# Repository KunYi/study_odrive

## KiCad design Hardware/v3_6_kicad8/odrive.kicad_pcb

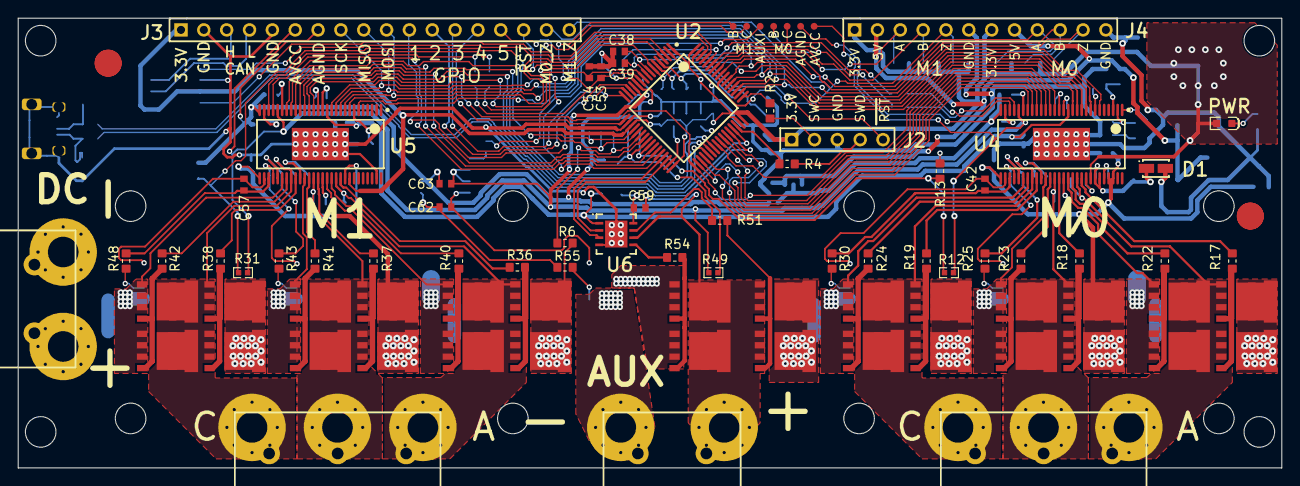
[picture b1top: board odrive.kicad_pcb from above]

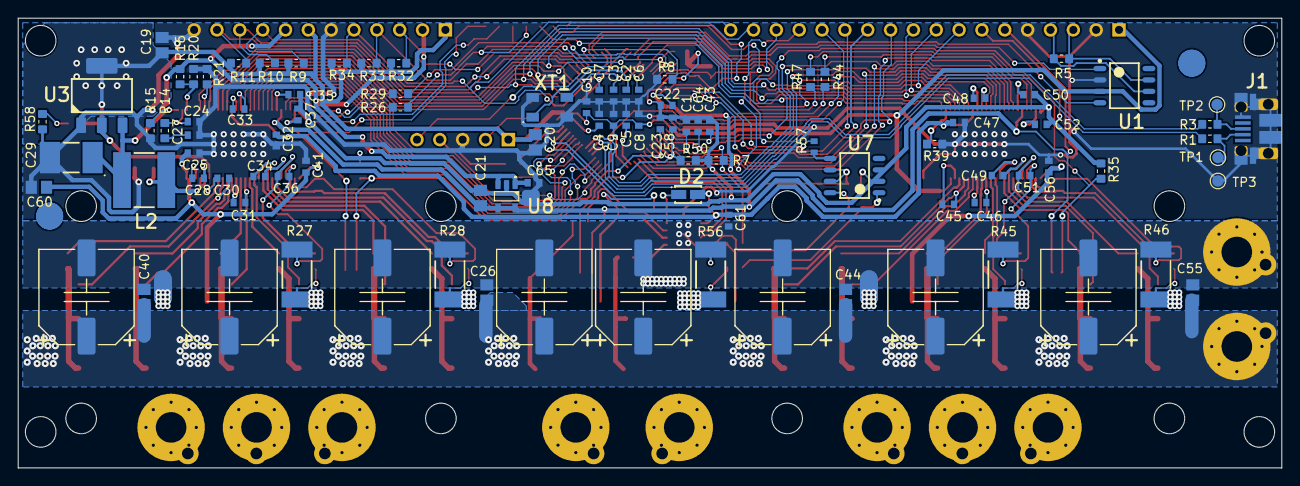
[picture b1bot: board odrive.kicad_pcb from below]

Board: 2 copper layers, 140.5 x 50.0 mm, 217 parts (109 on the bottom side), 152 nets.

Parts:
C1, C4, C5, C23, C32, C35, C37, C43, C47, C50, C52, C58, C61, C65: 2.2µF; CAPC1608X09L
C2, C3: 10pF; CAPC1608X09L
C6, C7, C8, C9, C10, C22, C25, C28, C30, C31, C34, C41, C45, C46, C49, C56, C59, C63: 0.1uF; CAPC1608X09L
C11, C12, C13, C14, C15, C16, C17, C18: 470uF; CAP_ELEC_SIZE_G
C19, C20, C21, C26, C40, C44, C55, C60: 4.7uF; CAPC2012X09N
C24: 82pF; CAPC1608X09L
C27: 270pF; CAPC1608X09L
C29: 68uF; CAPCP6032X28N
C33, C48: 0.022µF; CAPC1608X09L
C36, C38, C39, C42, C51, C53, C54, C57, C62, C64: 2200pF; CAPC1608X09L
D1, D2: DIOM2717X10N
FID1, FID2, FID3, FID4: FIDUCIAL
H1, H2, H3, H4, H5, H6, H7, H8, H9, H10, H11, H12: M3 Hole
J1: USB_0103594-0001LF
J2: HDR1X5
J3: Leftheader; HDR1X18
J4: Rightheader; HDR1X12
J7, J8, J11, J12, J13, J16, J17, J18, J21, J22: M3 Spade Hole
J9, J23: 1868076
J14, J19: 1704936
L2: 22uH; INDC6060X28N
LED1: Green; LED-0603-GREEN
NT1: NetTie_2mm
NT2, NT3, NT4, NT5, NT6, NT7, NT8, NT9, NT10, NT11: 0.25mm; NetTie_0.25mm
Q1, Q3, Q5, Q7, Q8, Q9, Q10, Q11, Q12, Q13, Q15, Q17, Q19, Q20, Q21, Q22, Q23, Q24, Q26, Q27, Q28: SO8FL
Q2, Q4, Q6, Q14, Q16, Q18, Q25: FILL_FOOTPRINT; SO8FL_FILL
R1, R2, R3, R4, R26, R29, R44, R47: 22R; RESC1608X55N
R5, R25, R30, R43, R48, R55: 120R; RESC1608X55N
R6: 10K; RESC1608X55N
R7, R58: 1k; RESC1608X55N
R8, R14: 47K; RESC1608X55N
R9, R10, R11, R13, R20, R32, R33, R34, R35, R50: 3.3k; RESC1608X55N
R12, R31, R49: 10k; RESC1005X40N
R15: 220k; RESC1608X55N
R16, R21, R39: 18k; RESC1608X55N
R17, R18, R19, R22, R23, R24, R36, R37, R38, R40, R41, R42, R51, R54: 2.2R; RESC1608X55N
R27, R28, R45, R46, R56: 500uOhm; RESC6432X09N
R57: 120R; RESC1608X06L
TP1, TP2, TP3: TESTPOINT; TP-R60
TP4, TP5, TP6, TP7, TP8, TP9, TP10: TESTPOINT; TP-R30
U1: SN65HVD232D; SOIC127P600X175-8N
U2: STM-LQFP64_N
U3: 3.3V; SOT223
U4, U5: TSSOP50P810X120_HS-57N
U6: SON80P400X80_HS-9N
U7: SOIC127P600X175-8N
U8: 3.3V; SOT23-5
XT1: 8 MHz; DFN220P320X110-4N

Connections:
5V: C29.1, C65.2, J4.2, J4.8, L2.2, R16.1, U3.3, U8.1, U8.3
AGND: C1.1, C21.1, C22.2, C23.1, C35.1, C37.1, C38.2, C39.2, C43.1, C50.1, C52.1, C53.2, C54.2, C58.1, C63.2, C64.2, J3.7, NT1.2, R7.1, R13.2, R35.2, R50.2, TP5.1, U2.12, U4.28, U5.28, U7.2, U7.3, U8.2
AUX_H_1: U2.30, U6.2
AUX_I_1: C64.1, R57.2, TP10.1, U2.21
AUX_L_1: U2.29, U6.3
AUX_TEMP_1: C58.2, R49.1, R50.1, U2.24
AVCC: C21.2, C22.1, C63.1, J3.6, R12.2, R31.2, R49.2, TP4.1, U2.13, U4.24, U5.24, U7.6, U7.7, U8.4, U8.5
BOOT0_1: R8.2, U2.60
CAN_D_1: U1.1, U2.62
CAN_H_1: J3.3, R5.2, U1.7
CAN_L_1: J3.4, R5.1, U1.6
CAN_R_1: U1.4, U2.61
DCBUS: C11.1, C12.1, C13.1, C14.1, C15.1, C16.1, C17.1, C18.1, C25.1, C26.2, C40.2, C41.1, C44.2, C55.2, C56.1, C60.2, J7.1, J9.2, Q1.D, Q2.D, Q3.D, Q4.D, Q5.D, Q6.D, Q13.D, Q14.D, Q15.D, Q16.D, Q17.D, Q18.D, Q25.D, Q26.D, R6.2, U4.29, U4.53, U4.54, U5.29
EN_GATE_1: U2.33, U4.16, U5.16
GH_A_2: R17.2, U4.47
GH_A_3: R36.1, U5.47
GH_B_2: R18.2, U4.42
GH_B_3: R37.1, U5.42
GH_C_2: R19.2, U4.37
GH_C_3: R38.1, U5.37
GL_A_2: R22.2, U4.45
GL_A_3: R40.1, U5.45
GL_B_2: R23.2, U4.40
GL_B_3: R41.1, U5.40
GL_C_2: R24.2, U4.35
GL_C_3: R42.1, U5.35
GND: C2.2, C3.2, C4.1, C5.1, C6.1, C7.2, C8.2, C9.2, C10.2, C19.1, C20.1, C24.2, C25.2, C27.2, C29.2, C32.1, C41.2, C47.1, C56.2, C60.1, C65.1, D1.A, J1.5, J1.SH, J2.3, J3.2, J3.5, J4.6, J4.12, NT1.1, NT7.1, R8.1, R15.2, R20.2, R21.2, R39.2, R58.2, TP3.1, U1.2, U2.18, U2.63, U3.1, U4.57, U5.55, U5.57, XT1.G
GPIO_1_1: J3.11, U2.14
GPIO_2_1: J3.12, U2.15
GPIO_3_1: J3.13, U2.16
GPIO_4_1: J3.14, U2.17
GPIO_5_1: J3.15, U2.28
GVDD: C32.2, C47.2, C61.2, D2.A, U4.13, U5.13, U6.1
M0_AH_1: U2.41, U4.17
M0_AL_1: U2.34, U4.18
M0_BH_1: U2.42, U4.19
M0_BL_1: U2.35, U4.20
M0_CH_1: U2.43, U4.21
M0_CL_1: U2.36, U4.22
M0_DC_CAL_1: U2.40, U4.12
M0_ENC_A_1: J4.9, R9.1, U2.56
M0_ENC_B_1: J4.10, R10.1, U2.57
M0_ENC_Z_1: J3.17, J4.11, R11.1, U2.50
M0_NCS_1: U2.2, U4.8
M0_SO1_1: C38.1, R26.2, TP6.1, U2.8
M0_SO2_1: C39.1, R29.2, TP7.1, U2.9
M0_TEMP_1: C23.2, R12.1, R13.1, U2.25
M1_AH_1: U2.37, U5.17
M1_AL_1: U2.23, U5.18
M1_BH_1: U2.38, U5.19
M1_BL_1: U2.26, U5.20
M1_CH_1: U2.39, U5.21
M1_CL_1: U2.27, U5.22
M1_DC_CAL_1: U2.4, U5.12
M1_ENC_A_1: J4.3, R32.2, U2.58
M1_ENC_B_1: J4.4, R33.2, U2.59
M1_ENC_Z_1: J3.18, J4.5, R34.2, U2.55
M1_NCS_1: U2.3, U5.8
M1_SO1_1: C53.1, R44.2, TP8.1, U2.11
M1_SO2_1: C54.1, R47.2, TP9.1, U2.10
M1_TEMP_1: C43.2, R31.1, R35.1, U2.20
NFAULT_1: U2.54, U4.6, U5.6
NRST_1: C6.2, J2.5, J3.16, U2.7
NetC2_1: C2.1, U2.6, XT1.1
NetC3_1: C3.1, U2.5, XT1.3
NetC4_2: C4.2, U2.47
NetC5_2: C5.2, U2.31
NetC24_1: C24.1, R14.1, U4.2
NetC27_1: C27.1, R14.2
NetC28_1: C28.1, D1.K, L2.1, U4.50, U4.51
NetC28_2: C28.2, U4.52
NetC30_2: C30.2, U4.48
NetC31_2: C31.2, U4.43
NetC33_1: C33.1, U4.14
NetC33_2: C33.2, U4.15
NetC34_2: C34.2, U4.38
NetC35_2: C35.2, U4.23
NetC36_1: C36.1, R25.2, U4.33
NetC37_2: C37.2, U4.27
NetC42_1: C42.1, R30.2, U4.31
NetC45_2: C45.2, U5.48
NetC46_2: C46.2, U5.43
NetC48_1: C48.1, U5.14
NetC48_2: C48.2, U5.15
NetC49_2: C49.2, U5.38
NetC50_2: C50.2, U5.23
NetC51_1: C51.1, R43.2, U5.33
NetC52_2: C52.2, U5.27
NetC57_1: C57.1, R48.2, U5.31
NetC59_1: C59.1, D2.K, U6.8
NetC59_2: C59.2, J21.1, J23.2, Q25.S, Q26.S, Q27.D, Q28.D, U6.6
NetC62_1: C62.1, R55.1, U7.1
NetC62_2: C62.2, NT6.1, U7.8
NetJ1_2: J1.2, R1.2, TP1.1
NetJ1_3: J1.3, R3.2, TP2.1
NetJ2_2: J2.2, R2.1
NetJ2_4: J2.4, R4.1
NetJ22_1: J22.1, J23.1, R55.2, R56.1
NetLED1_K: LED1.K, R58.1
NetQ1_G: Q1.G, Q2.G, R17.1
NetQ3_G: Q3.G, Q4.G, R18.1
NetQ5_G: Q5.G, Q6.G, R19.1
NetQ7_G: Q7.G, Q8.G, R22.1
NetQ9_G: Q9.G, Q10.G, R23.1
NetQ11_G: Q11.G, Q12.G, R24.1
NetQ13_G: Q13.G, Q14.G, R36.2
NetQ15_G: Q15.G, Q16.G, R37.2
NetQ17_G: Q17.G, Q18.G, R38.2
NetQ19_G: Q19.G, Q20.G, R40.2
NetQ21_G: Q21.G, Q22.G, R41.2
NetQ23_G: Q23.G, Q24.G, R42.2
NetQ25_G: Q25.G, Q26.G, R51.2
NetQ27_G: Q27.G, Q28.G, R54.2
NetR15_1: R15.1, U4.1
NetR16_2: R16.2, R20.1, U4.3
NetR21_1: R21.1, U4.7
NetR26_1: R26.1, U4.25
NetR29_1: R29.1, U4.26
NetR39_1: R39.1, U5.7
NetR44_1: R44.1, U5.25
NetR47_1: R47.1, U5.26
NetR51_1: R51.1, U6.7
NetR54_1: R54.1, U6.5
NetR57_1: R57.1, U7.5
PGND: C11.2, C12.2, C13.2, C14.2, C15.2, C16.2, C17.2, C18.2, C26.1, C40.1, C44.1, C55.1, C61.1, J8.1, J9.1, NT2.2, NT3.2, NT4.2, NT5.2, NT6.2, NT7.2, Q7.S, Q8.S, Q19.S, Q20.S, Q27.S, Q28.S, R27.1, R28.1, R45.1, R46.1, R56.2, U4.44, U5.44, U6.4, U6.9
SH_A_2: C30.1, J11.1, J14.3, Q1.S, Q2.S, Q7.D, Q8.D, U4.46
SH_A_3: C45.1, J16.1, J19.3, Q13.S, Q14.S, Q19.D, Q20.D, U5.46
SH_B_2: C31.1, J12.1, J14.2, Q3.S, Q4.S, Q9.D, Q10.D, U4.41
SH_B_3: C46.1, J17.1, J19.2, Q15.S, Q16.S, Q21.D, Q22.D, U5.41
SH_C_2: C34.1, J13.1, J14.1, Q5.S, Q6.S, Q11.D, Q12.D, U4.36
SH_C_3: C49.1, J18.1, J19.1, Q17.S, Q18.S, Q23.D, Q24.D, U5.36
SL_B_2: NT8.2, Q9.S, Q10.S, R27.2, U4.39
SL_B_3: NT10.2, Q21.S, Q22.S, R45.2, U5.39
SL_C_2: NT9.2, Q11.S, Q12.S, R28.2, U4.34
SL_C_3: NT11.2, Q23.S, Q24.S, R46.2, U5.34
SN1_2: NT8.1, R25.1
SN1_3: NT10.1, R43.1
SN2_2: NT9.1, R30.1
SN2_3: NT11.1, R48.1
SP1_2: C36.2, NT2.1, U4.32
SP1_3: C51.2, NT4.1, U5.32
SP2_2: C42.2, NT3.1, U4.30
SP2_3: C57.2, NT5.1, U5.30
SPI_MISO_1: J3.9, U2.52, U4.10, U5.10
SPI_MOSI_1: J3.10, U2.53, U4.9, U5.9
SPI_SCK_1: J3.8, U2.51, U4.11, U5.11
SWCLK_1: R2.2, U2.49
SWDIO_1: R4.2, U2.46
USB_DM_1: R1.1, U2.44
USB_DP_1: R3.1, U2.45
VBUS_S_1: C1.2, R6.1, R7.2, U2.22
VCC: C7.1, C8.1, C9.1, C10.1, C19.2, C20.2, J2.1, J3.1, J4.1, J4.7, LED1.A, R9.2, R10.2, R11.2, R32.1, R33.1, R34.1, U1.3, U2.1, U2.19, U2.32, U2.48, U2.64, U3.2, U3.4, U4.49, U5.49

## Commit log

2025-03-18 import latest open source and hardware of Odrive
    for my study
    Hardware
    - branch:master
    - commit id:079f30ac58f193226fcc552e4d6ba24553027ee1
    - only latest v3.6
    - convert Altium design to KICAD v8 format
2025-03-18 add comment for TIM1/TIM8 and TIM2 for motors
    TIM1/TIM8 for Motors PWM Generator
    - TIM1 for M0
    - TIM8 for M1
    TIM2 for AUX (Break resistor) PWM Generator
2025-03-18 modify aux schematic for gate driver value
2025-03-19 add Code struucture.rst
2025-03-19 assign AD8418 to current amplifier of AUX
2025-03-21 update somethings for odrive architecture
2025-03-22 update code structure and preview env
2025-03-23 correct PWM timing
2025-03-24 update doc
2025-03-25 update DCBUS voltage divider for 48/56V
2025-03-25 update docs/comments
2025-03-26 add interrupt table
2025-03-26 update about sampling timing in doc
2025-03-26 add PWM timing update describle
2025-03-27 add transformation.py for demo
2025-03-27 make clark/park transformation to functions
2025-03-27 add SVMs status
2025-03-27 add about clarke transformation
2025-03-28 update documents for clarke transmation
2025-03-31 continue re-write doc about clarke transmation
2025-04-01 add clarke transform pdf by browser printing
2025-04-01 disable some bugs feature
2025-04-01 add trigonmetric
2025-04-02 fixed some typo about clarke transmation
    update clarke transmation document
    we find some typo and format error
2025-04-04 add documents for park transformation
2025-04-07 fixed some typo for park transformation
2025-07-09 add my board config
